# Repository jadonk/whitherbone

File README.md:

# whitherbone

Whithervanes: a neurotic, early worrying system are weathervanes controlled by the climate of fear on the Internet. They were first presented on five buildings in the seaside town of Folkestone, UK as part of the 2014 Folkestone Triennial. The Whithervanes parse newsfeeds looking for predetermined keywords related to fear (e.g. natural disaster, economic collapse, war, etc.) When fear is encountered the chickens respond by rotating away at increasing speeds from fear hot-spots and illuminating different colors triggered by specific levels of fear. Subsequently, 3 more full-size Whithervanes have been commissioned by Locust Projects in Miami for 2018.

We've been asked many times how people can have their own Whithervane. So, we are making the Whithervanes Open Hardware Kit. A prototype version was included in the “Are you talking to me?” exhibition currently in St. Etienne, France. We want to make the Whithervanes Open Hardware Kit a PocketBeagle derivative (Whitherbone), and need some help to do this.

http://www.whithervanes.com/

## Fan
| Pin | Signal |
| --- | ------ |
| 1   | GND    |
| 2   | +5V    |
| 3   | +5V    |
| 4   | GND    |

## Neopixel ring (LED)

| Pin | Signal | CPU ball | PRU  | SPI    | GPIO | 
| --- | ------ | -------- | ---- | ------ | ---- |
| 1   | GND    |          |      |        |      | 
| 2   | Data (DOUT)  | B2       | 0.2  | 1-MOSI | 112  | 
| 3   | +5V    |          |      |        |      | 
| 4   | GND    |          |      |        |      | 

## Motor

### Connector

| Pin | Signal       | Wires  |
| --- | ------------ | ------ |
| 1   | Coil 1+ (A+) | Red    |
| 2   | Coil 1- (A-) | Green  |
| 3   | Coil 2- (B-) | Blue   |
| 4   | Coil 2+ (B+) | Yellow | 

### Control signals

| Ball | GPIO | Signal |
| ---- | ---- | ------ |
| T4   | 22   | Step |
| P5   | 23   | Direction |
| R5   | 26   | Reset |
| T5   | 27   | uS1 |
| P6   | 44   | uS2 |
| R6   | 45   | uS3 |
| T6   | 46   | Enable |
| P7   | 47   | Sleep

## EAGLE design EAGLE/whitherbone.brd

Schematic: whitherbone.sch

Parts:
ANT1, ANT2: RECE.20279.001E.01; U-FL3P-SMD-2.6X2.6X1.0MM
C1: TLJB227M006R0500; AVX-B
C2, C8, C26, C38, C84: 1uF 10V; C0402
C3, C7: 47uF DNP; C1206
C4, C5, C18, C29, C30, C32, C33, C35, C36, C70, C74, C75, C79, C82, C83: 10uF 25V; C0805
C6, C20, C25, C27, C28, C31, C34, C44, C53, C61, C62, C63, C64, C65, C66, C69, C71, C72, C73, C76, C77, C78, C80, C81: 100nF 25V; C0402
C9, C10: 10pF; C0402
C11: 1nF 1000V; C1206
C12, C13, C14, C15: 18pF 50V; C0402
C16, C24: 100uF 16V; C1210
C17, C19, C56, C68: 100nF 50V; C0805
C21, C22: 22uF 16V; C1206
C23: 75pF 50V; C0402
C37, C40: DNI; C0402
C39, C41, C42, C43, C45, C46, C47, C49, C50, C52, C54, C55, C57, C58, C59, C60: 33pF 50V; C0402
C48, C51: 47uF 25V; ELECTRO-SMD-C-6MM
C67: 220nF; C0402
D1, D5, D6, D7, D8: Red; LED-0603
D2, D3, D4: Green; LED-0603
D9, D10, D11, D12, D13: DF2S6.8FS; SOD-923
F1: MF-FSMF010X; F0603
FUD1, FUD2, FUD3, FUD4, FUD5, FUD6: FIDUCIAL; FIDUCIAL_40MIL
IC1, IC2: TPD4S012DRYR; SON6-0.5-1.45X1X0.55MM
J1: ST-USB-01H2; MICRO-USB5+5P-SMD-0.65-7.2X5.06MM
J2: DC-044; DCJ3P-11.6X9.6X7.0MM
J3: ST-TF-003J; MICRO-SD9+4P-SMD-16.1X14.5X1.85MM
J4: 6p-2.54 DNP; H6-2.54
J5: WY-1223; H4-2.54-10.2X5.6MM
J6: ST-HD-010; HDMI19P-0.5-15X12.15X6.18MM
J7, J8: 2510S-4P(T); H4-2.54
JP2: ST-USB-003A; USB4+2-2.0-90D
L1, L2, L7, L8, L9: BLM15PD121SN1D; L0402
L3: IHLP3232DZER100M01; INT2-7.268-8.64X8.18X4MM
L4, L5: BLM21PG331SN1D; L0805
L6: LQH44PN1R0NP0L; L4.4X3.0MM
L10: WPN201610MR47MT; L201610
MGT1, MGT2, MGT3, MGT4: MOUNTING_HOLE
Q1, Q2, Q3: BSS138W-7-F; SOT-323
Q4: MMBT2907A; SOT-323
R1, R2, R18, R51, R52, R53, R54: 1.5k 1%; R0402
R3, R21, R62, R69, R70: 10k 1%; R0402
R4, R6, R7, R8, R9, R10, R63, R67, R68, R71, R72, R73, R74, R75, R81, R82, R83, R84, R87, R88, R89, R90, R91, R92, R93, R94, R98, R100, R106, R108, R109, R112, R119: 10k; R0402
R5, R11, R12, R31, R79, R96: 1k; R0402
R13, R14, R15, R16, R19, R22, R25, R26, R27, R28, R29: 33R; R0402
R17: 499R; R0402
R20: 40.2k 1%; R0402
R23, R24, R47, R64, R65, R66, R85, R116, R117, R118: 0R; R0402
R30: DNP 10k; R0402
R32: 100K, 1%, DNI; R0402
R33, R34, R35, R36, R37, R38, R39, R40, R41, R42, R43, R44, R45, R46, R49, R50, R58, R60, R80, R113, R114: 100k 1%; R0402
R48, R97: 0R; R1206
R55: 1M 1%; R0402
R56: 1M, 1%, DNI; R0402
R57: 560k 1%; R0402
R59: 49.9R 1%; R0402
R61: 13.3k 1%; R0402
R76: 51k 1%; R0402
R77: 1.3k 1%; R0402
R78: 240k 1%; R0402
R86, R101: DNP; R0402
R95, R102, R103, R115: 22R; R0402
R99: 5.6K 1%; R0402
R104, R105: 2k; R0402
R107: 33k; R0402
R110, R111: 0.1R; R1206
SW1, SW2: SKRPABE010; BUTTON4P-SMD-4.5X3.2X2.5MM
TP1: PAD-TEST-POINT'4545'; TP_4545
TP2, TP3, TP4, TP9, TP11, TP12, TP13, TP14, TP15, TP16, TP21, TP22, TP23, TP24: TPB0,65; TP_B0,65
TP5, TP6, TP7, TP8, TP26: TESTPAD/W_HOLE_1X1
TP10, TP34: TEST-POINT-D65/35; TP-D65/35MIL
TP17, TP18, TP19, TP20, TP25, TP27, TP28, TP29, TP30, TP31, TP32: TEST-POINT'4545'; TP-D45MIL
U1: OSD3358-512M-BSM; BGA256-1.27-21X21MM
U2: SN74LVC1G07DCKR; 5P-SMD-2X1.2X1MM
U3: ATL431AIDBZR; SOT-23
U4: WL1835MODGBMOCT; MODULE100P-0.7-13.5X13.2MM
U5: APX811-44UG-7; SOT143-R
U6: TPS54302; SOT-23-6
U7: TPS2051BDGNR; MSOP8-0.65-3X3MM
U8, U16: TLV62569DBVT; SOT-23-5
U9: SN74LVC1G125DCKR; SOT-353
U10: SN74LVC2G241DCUR; DCU8
U11: IT66121FN; QFN64-0.5-9X9MM
U12: A4988SETTR-T; QFN-28-5MM
U13, U14: ESD-RCLAMP0524P; ESD10P-0.5-2.5X1X0.58MM
VR1: EVM3GSX50B14; ADJR3-SMD-3.6X3.3MM
X1: ST3215SB32768H5HPWAA; X2-SMD-3.2X1.5X0.55MM
Y1: CX3225GB24000P0HPQCC; CRYSTAL-TXC-7A

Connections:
1.8V-WIFI: C2.1, C7.2, C8.1, L1.2, R4.1, R6.1, R7.1, R8.1, R9.1, R10.1, R30.1, U4.38 (VIO)
3.3V-WIFI: C3.2, C4.1, C5.1, C6.1, L2.2, R5.2, R11.2, R12.2, U4.46 (VBAT_IN1), U4.47 (VBAT_IN2)
12VDC: C48.+, C51.+, C68.2, R97.2, U12.22 (VBB1), U12.28 (VBB2)
AGND: C25.2, C27.2, C28.2, R66.2, U1.A9 (AGND_ADC)
AIN7: U1.D6 (PMIC_MUX_OUT), U1.D7 (AIN7)
BAT_SENSE: TP6.P$1, U1.N7 (PMIC_BAT_SENSE)
BT_EN: Q3.1 (G), U1.H15 (MII1_TXD0), U4.41 (BT_EN)
BT_HCI_CTS: R14.2, U1.D13 (MDC)
BT_HCI_RTS: R13.2, U1.E13 (MDIO)
BT_HCI_RX: R16.2, U1.D15 (MII1_RXD2)
BT_HCI_TX: R15.2, U1.D14 (MII1_RXD3)
B_UART0_RX: J4.4, R80.2, U10.2 (1A)
B_UART0_TX: J4.5, U10.3 (2Y)
CEC: D12.1 (2), J6.13 (CE_REMOTE), R106.2, U11.17 (CEC)
CGND: C11.2, J1.P1 (GND), J1.P3 (GND), J1.P4 (GND), J1.P5 (GND), J1.P6 (GND), J3.G2, J3.G3, J3.G4 (G3), J6.PAD (SHELL1), J6.PAD1 (SHELL2), J6.PAD2 (SHELL3), J6.PAD3 (SHELL4), JP2.SG1 (GND), JP2.SG2 (GND), MGT1.P$1, MGT2.P$1, MGT3.P$1, MGT4.P$1, R48.2
CK_N: J6.12 (CK-), U11.21 (TXCM), U14.5, U14.6
CK_P: J6.10 (CK+), U11.22 (TXCP), U14.4, U14.7
CLKOUT2: C37.2, R79.2, R96.2, U4.36 (EXT_32K)
COILA+: J5.1, U12.21 (OUT1B)
COILA-: J5.2, U12.24 (OUT1A)
COILB+: J5.4, U12.1 (OUT2B)
COILB-: J5.3, U12.26 (OUT2A)
CUR_REF: U12.17 (REF), VR1.2 (3)
D0_N: J6.9 (D0-), U11.24 (TX0M), U14.2, U14.9
D0_P: J6.7 (D0+), U11.25 (TX0P), U14.1, U14.10
D1_N: J6.6 (D1-), U11.26 (TX1M), U13.5, U13.6
D1_P: J6.4 (D1+), U11.27 (TX1P), U13.4, U13.7
D2_N: J6.3 (D2-), U11.29 (TX2M), U13.2, U13.9
D2_P: J6.1 (D2+), U11.30 (TX2P), U13.1, U13.10
DDC_SCL: D9.1 (2), J6.15 (DDC_CLK), R102.2, R104.2
DDC_SDA: D10.1 (2), J6.16 (DDC_DATA), R103.2, R105.2
DIR(GPIO23): R88.1, U1.P5 (GPMC_AD9), U12.19 (DIR)
EEPROM_WP: TP10.P1, U1.M2 (EEPROM_WP), U1.N3 (GPMC_BEN0_CLE)
ENABLE(GPIO46): R94.1, U1.T6 (GPMC_AD14), U12.2 (ENABLE)
GND: ANT1.GND1, ANT1.GND2, ANT2.GND1, ANT2.GND2, C1.-, C2.2, C3.1, C4.2, C5.2, C6.2, C7.1, C8.2, C11.1, C16.1, C17.1, C18.1, C20.2, C21.1, C22.1, C24.2, C26.1, C29.1, C30.1, C31.2, C32.2, C33.1, C34.2, C35.1, C36.1, C37.1, C38.1, C39.2, C40.1, C41.2, C42.2, C43.2, C44.1, C45.2, C46.2, C47.2, C48.-, C49.2, C50.2, C51.-, C52.2, C53.2, C54.2, C55.2, C57.2, C58.2, C59.2, C60.2, C61.1, C62.1, C63.1, C64.1, C65.1, C66.1, C67.2, C69.1, C70.1, C71.1, C72.1, C73.1, C74.1, C75.1, C76.1, C77.1, C78.1, C79.1, C80.1, C81.1, C82.1, C83.1, C84.1, D9.2 (1), D10.2 (1), D11.2 (1), D12.2 (1), D13.2 (1), IC1.4 (GND), IC2.4 (GND), J1.5 (GND), J2.-, J2.CDN, J3.6 (VSS), J4.1, J6.2 (D2_SHIELD), J6.5 (D1_SHIELD), J6.8 (D0_SHIELD), J6.11 (CK_SHIELD), J6.17 (GND), J7.1, J7.4, J8.1, J8.4, JP2.4 (GND), Q1.2 (S), Q2.2 (S), Q3.2 (S), R3.2, R18.2, R32.1, R33.1, R35.1, R36.1, R37.1, R38.1, R39.1, R40.1, R41.1, R42.1, R43.1, R46.1, R48.1, R49.1, R50.1, R51.2, R52.2, R53.2, R54.2, R58.1, R61.1, R62.2, R64.1, R70.1, R77.1, R79.1, R80.1, R94.2, R98.2, R99.1, R101.1, R107.1, R108.2, R109.1, R110.1, R111.1, R114.1, R119.2, SW1.1, SW1.2, SW2.1, SW2.2, TP8.P$1, U1.D8 (DGND), U1.D9 (DGND), U1.E5 (DGND), U1.E6 (DGND), U1.E7 (DGND), U1.E8 (DGND), U1.E9 (DGND), U1.E10 (DGND), U1.E11 (DGND), U1.E12 (DGND), U1.F5 (DGND), U1.F12 (DGND), U1.G5 (DGND), U1.G12 (DGND), U1.H4 (DGND), U1.H5 (DGND), U1.H12 (DGND), U1.H13 (DGND), U1.J4 (DGND), U1.J5 (DGND), U1.J12 (DGND), U1.J13 (DGND), U1.K5 (DGND), U1.K12 (DGND), U1.L5 (DGND), U1.L12 (DGND), U1.M5 (DGND), U1.M6 (DGND), U1.M7 (DGND), U1.M8 (DGND), U1.M9 (DGND), U1.M10 (DGND), U1.M11 (DGND), U1.M12 (DGND), U1.N8 (DGND), U1.N9 (DGND), U2.3 (GND), U4.1 (GND1), U4.7 (GND2), U4.9 (GND3), U4.15 (GND4), U4.16 (GND5), U4.17 (GND6), U4.19 (GND7), U4.20 (GND8), U4.23 (GND9), U4.24 (GND10), U4.28 (GND11), U4.29 (GND12), U4.30 (GND13), U4.31 (GND14), U4.33 (GND15), U4.34 (GND16), U4.35 (GND17), U4.37 (GND18), U4.39 (GND19), U4.44 (GND20), U4.45 (GND21), U4.48 (GND22), U4.49 (GND23), U4.54 (GND24), U4.55 (GND25), U4.59 (GND26), U4.61 (GND27), U4.63 (GND28), U4.64 (GND29), U4.G1, U4.G2, U4.G3, U4.G4, U4.G5, U4.G6, U4.G7, U4.G8, U4.G9, U4.G10, U4.G11, U4.G12, U4.G13, U4.G14, U4.G15, U4.G16, U4.G17, U4.G18, U4.G19, U4.G20, U4.G21, U4.G22, U4.G23, U4.G24, U4.G25, U4.G26, U4.G27, U4.G28, U4.G29, U4.G30, U4.G31, U4.G32, U4.G33, U4.G34, U4.G35, U4.G36, U5.1 (GND), U6.1 (GND), U7.1 (GND), U7.9 (THERMAL), U8.2 (GND), U9.1 (!OE), U9.3 (GND), U10.1 (*1OE), U10.4 (GND), U11.41 (D18), U11.42 (D17), U11.43 (D16), U11.50 (D9), U11.52 (D8), U11.59 (D2), U11.60 (D1), U11.61 (D0), U11.65 (GND), U12.3 (GND), U12.18 (GND), U12.PAD (GND_PAD), U13.3, U13.8, U14.3, U14.8, U16.2 (GND), VR1.1
HDMI_1V2: C61.2, C62.2, C63.2, C64.2, C65.2, C66.2, C82.2, C83.2, L10.2, R113.2, TP18.T, U11.8 (IVDD12), U11.18 (PVCC12), U11.23 (AVCC12), U11.28 (DVDD12), U11.35 (IVDD12), U11.56 (IVDD12)
HDMI_3V3: C69.2, C71.2, C73.2, C76.2, C77.2, C78.2, L8.2, R81.1, R82.1, R83.1, R84.1, R100.1, R106.1, R109.2, TP19.T, U11.1 (OVDD), U11.9 (VCC33), U11.13 (OVDD33), U11.19 (PVCC33), U11.34 (OVDD), U16.1 (EN)
HDMI_5V: C84.2, D11.1 (2), F1.2, J6.18 (+5V), R104.1, R105.1, TP20.T
HDMI_AUDBCLK: U1.A1 (MCASP0_ACLKX), U11.7 (SCK/MCLK)
HDMI_AUDDOUT: R85.1, R86.1, U1.B1 (MCASP0_AHCLKR)
HDMI_AUDWCLK: U1.A2 (MCASP0_FSX), U11.6 (WS)
HDMI_INT: R83.2, U1.T15 (GPMC_A9), U11.10 (INT)
HDMI_NRST: C38.2, R84.2, U11.33 (SYSRSTN)
HPD: D13.1 (2), J6.19 (HPD), R107.2, U11.14 (HPD)
I2C0_SCL: R1.1, U1.C10 (I2C0_SCL), U1.D10 (PMIC_SCL)
I2C0_SDA: R2.1, U1.C11 (I2C0_SDA), U1.D11 (PMIC_SDA)
I2C2_SCL: R82.2, U1.A10 (UART1_RTSN), U11.12 (PCSCL)
I2C2_SDA: R81.2, U1.B10 (UART1_CTSN), U11.11 (PCSDA)
LCD_DATA0: C60.1, R50.2, U1.G3 (LCD_DATA0), U11.58 (D3)
LCD_DATA1: C59.1, R49.2, U1.G2 (LCD_DATA1), U11.57 (D4)
LCD_DATA2: C58.1, R46.2, U1.G1 (LCD_DATA2), U11.55 (D5)
LCD_DATA3: C57.1, R45.1, U1.H3 (LCD_DATA3), U11.54 (D6)
LCD_DATA4: C55.1, R44.1, U1.H2 (LCD_DATA4), U11.53 (D7)
LCD_DATA5: C46.1, R43.2, U1.H1 (LCD_DATA5), U11.49 (D10)
LCD_DATA6: C45.1, R42.2, U1.J3 (LCD_DATA6), U11.48 (D11)
LCD_DATA7: C43.1, R41.2, U1.J2 (LCD_DATA7), U11.47 (D12)
LCD_DATA8: C42.1, R40.2, U1.J1 (LCD_DATA8), U11.46 (D13)
LCD_DATA9: C41.1, R39.2, U1.K3 (LCD_DATA9), U11.45 (D14)
LCD_DATA10: C39.1, R38.2, U1.K2 (LCD_DATA10), U11.44 (D15)
LCD_DATA11: C54.1, R37.2, U1.K1 (LCD_DATA11), U11.40 (D19)
LCD_DATA12: C52.1, R36.2, U1.L3 (LCD_DATA12), U11.39 (D20)
LCD_DATA13: C50.1, R35.2, U1.L2 (LCD_DATA13), U11.38 (D21)
LCD_DATA14: C49.1, R34.1, U1.L1 (LCD_DATA14), U11.37 (D22)
LCD_DATA15: C47.1, R33.2, U1.M3 (LCD_DATA15), U11.36 (D23)
LCD_DE: R118.2, U11.62 (DE)
LCD_HSYNC: R117.2, U11.63 (HSYNC)
LCD_PCLK: R115.2, U11.51 (PCLK)
LCD_VSYNC: R116.2, U11.64 (VSYNC)
LDO_PGOOD: TP22.TP, U1.N4 (PMIC_LDO_PGOOD), U1.N5 (RTC_PWRONRSTN)
MMC0_CD: J3.9 (CDN), R75.1, U1.C14 (SPI0_CS1)
MMC0_CLK: C40.2, J3.5 (SCLK), R71.1, R95.1
MMC0_CMD: J3.3 (DI), R68.1, U1.B16 (MMC0_CMD)
MMC0_DAT0: J3.7 (DO), R72.1, U1.A16 (MMC0_DAT0)
MMC0_DAT1: J3.8 (DATA1), R73.1, U1.A15 (MMC0_DAT1)
MMC0_DAT2: J3.1 (DATA2), R67.1, U1.C16 (MMC0_DAT2)
MMC0_DAT3: J3.2 (CS), R74.1, U1.C15 (MMC0_DAT3)
MS1(GPIO27): R89.1, U1.T5 (GPMC_AD11), U12.9 (MS1)
MS2(GPIO44): R90.1, U1.P6 (GPMC_AD12), U12.10 (MS2)
MS3(GPIO45): R91.1, U1.R6 (GPMC_AD13), U12.11 (MS3)
MVCC: C53.1, L7.2, R87.2, R88.2, R89.2, R90.2, R91.2, R92.2, R93.2, R112.1, U12.15 (VDD)
unnamed: J1.1 (VCC), R47.1
unnamed: D5.-, R51.1
unnamed: R31.2, U5.2 (RESET#)
unnamed: TP9.TP, U1.F4 (VDDS_DDR)
unnamed: C81.2, F1.1, L9.2
unnamed: D4.-, R18.1
unnamed: R20.2, R21.1, U3.1 (R)
unnamed: Q4.1 (B), R17.1, U3.2 (K)
unnamed: D6.-, R52.1
unnamed: D7.-, R53.1
unnamed: D8.-, R54.1
unnamed: ANT2.D, C10.1
unnamed: ANT1.D, C9.1
unnamed: TP2.TP, U1.G4 (VDD_CORE)
unnamed: TP3.TP, U1.F13 (VDD_MPU)
unnamed: R96.1, U1.B4 (XDMA_EVENT_INTR1)
unnamed: TP4.TP, U1.G13 (VDDS_PLL)
unnamed: R95.2, U1.B15 (MMC0_CLK)
unnamed: C9.2, U4.32 (RF_ANT1)
unnamed: C10.2, U4.18 (RF_ANT2)
unnamed: TP29.T, U4.26 (GPIO2)
unnamed: R23.1, SW2.3, SW2.4
unnamed: TP31.T, U4.42 (WL_UART_DBG)
unnamed: TP32.T, U4.43 (BT_UART_DBG)
unnamed: R24.1, U2.4 (Y)
unnamed: TP17.T, U4.56 (BT_AUD_IN)
unnamed: R119.1, TP25.T, U4.57 (BT_AUD_OUT)
unnamed: R3.1, U1.M16 (RTC_KALDO_ENN)
unnamed: TP28.T, U4.60 (BT_AUD_CLK)
unnamed: TP30.T, U4.27 (GPIO1)
unnamed: D2.-, Q2.3 (D)
unnamed: R100.2, R101.2, U11.32 (PCADR)
unnamed: R98.1, U11.31 (ENTEST)
unnamed: R102.1, U11.16 (DDCSCL)
unnamed: R103.1, U11.15 (DDCSDA)
unnamed: R86.2, U11.2 (I2S3/SPDIF)
unnamed: R85.2, U11.5 (I2S0)
unnamed: TP27.T, U4.58 (BT_AUD_FSYNC)
unnamed: R99.2, U11.20 (REXT)
unnamed: R19.1, U4.6 (WL_SDIO_CMD)
unnamed: D1.+, R5.1
unnamed: D1.-, Q1.3 (D)
unnamed: R111.2, U12.27 (SENSE2)
unnamed: R110.2, U12.23 (SENSE1)
unnamed: C56.1, U12.4 (CP1)
unnamed: C56.2, U12.5 (CP2)
unnamed: R108.1, U12.13 (ROSC)
unnamed: C67.1, U12.8 (VREG)
unnamed: C68.1, U12.6 (VCP)
unnamed: D3.-, Q3.3 (D)
unnamed: D2.+, R11.1
unnamed: D3.+, R12.1
unnamed: R112.2, VR1.3 (2)
unnamed: J7.2, U9.4 (Y)
unnamed: R29.1, R30.2, U4.14 (WLAN_IRQ)
unnamed: R28.1, U4.13 (WL_SDIO_D3)
unnamed: R27.1, U4.12 (WL_SDIO_D2)
unnamed: R26.1, U4.11 (WL_SDIO_D1)
unnamed: R25.1, U4.10 (WL_SDIO_D0)
unnamed: R22.1, U4.8 (WL_SDIO_CLK)
unnamed: R115.1, U1.F1 (LCD_PCLK)
unnamed: R116.1, U1.F3 (LCD_VSYNC)
unnamed: L10.1, U16.3 (SW)
unnamed: R113.1, R114.2, U16.5 (FB)
unnamed: R76.2, R78.2, U8.5 (FB)
unnamed: L6.1, U8.3 (SW)
unnamed: R76.1, R77.2
unnamed: R117.1, U1.F2 (LCD_HSYNC)
unnamed: R57.1, R58.2, U6.5 (EN)
unnamed: R118.1, U1.E1 (LCD_AC_BIAS_EN)
unnamed: C19.2, U6.6 (BOOT)
unnamed: C19.1, L3.1, U6.2 (SW)
unnamed: C23.1, R59.1, R60.2
unnamed: C23.2, R60.1, R61.2, U6.4 (FB)
unnamed: R13.1, U4.50 (BT_HCI_RTS)
unnamed: R14.1, U4.51 (BT_HCI_CTS)
unnamed: R15.1, U4.52 (BT_HCI_TX)
unnamed: R16.1, U4.53 (BT_HCI_RX)
OSC0_GND: C12.2, C13.2, U1.N15 (OSC0_GND)
OSC0_IN: C12.1, R55.2, U1.P16 (OSC0_IN), Y1.P$2 (2)
OSC0_OUT: C13.1, R55.1, U1.N16 (OSC0_OUT), Y1.P$1 (1)
OSC1_GND: C14.2, C15.2, U1.B5 (OSC1_GND)
OSC1_IN: C14.1, R56.2, U1.A6 (OSC1_IN), X1.2
OSC1_OUT: C15.1, R56.1, U1.A5 (OSC1_OUT), X1.1
PMIC_INT: TP24.TP, U1.D4 (EXTINTN), U1.E4 (PMIC_NINT)
PMIC_MUX_IN: R69.1, R70.2, U1.N13 (PMIC_MUX_IN)
PMIC_NRESET: TP34.P1, U1.M13 (PMIC_NRESET)
PMIC_NWAKEUP: TP23.TP, U1.L4 (PMIC_NWAKEUP), U1.M4 (EXT_WAKEUP)
PMIC_PGOOD: U1.N12 (PMIC_PGOOD), U1.P11 (PWRONRSTN), U2.2 (A)
PWR_BUT: SW1.3, SW1.4, U1.T11 (PMIC_PB_IN)
PWR_EN: TP21.TP, U1.N10 (PMIC_POWER_EN), U1.N11 (PMIC_PWR_EN)
PWR_IN_12V: C16.2, C17.2, C18.2, J2.+, R57.2, R97.1, TP1.T, U6.3 (VIN)
RESET: R23.2, R24.2, U5.3 (MR#)
RESET(GPIO26): R93.1, U1.R5 (GPMC_AD10), U12.12 (RESET)
SLEEP(GPIO47): R92.1, U1.P7 (GPMC_AD15), U12.14 (SLEEP)
STEP(GPIO22): R87.1, U1.T4 (GPMC_AD8), U12.16 (STEP)
SYS_5V: C24.1, U7.2 (IN1), U7.3 (IN2)
SYS_ADC_1P8V: C28.1, R65.2, U1.A7 (SYS_ADC_1P8V)
SYS_RESETN: R31.1, R32.2, TP26.P$1, U1.R11 (WARMRSTN)
SYS_RTC_1P8V: Q4.3 (C), R20.1, TP14.TP, U1.K11 (SYS_RTC_1P8V), U1.L11 (SYS_RTC_1P8V), U2.5 (VCC), U3.3 (A)
SYS_VDD1_3P3V: C32.1, C34.1, C44.2, C70.2, C72.2, J3.4 (VDD), L8.1, R1.2, R2.2, R34.2, R44.2, R45.2, R63.1, R67.2, R68.2, R69.2, R71.2, R72.2, R73.2, R74.2, R75.2, TP12.TP, U1.F6 (SYS_VDD1_3P3V), U1.F7 (SYS_VDD1_3P3V), U1.G6 (SYS_VDD1_3P3V), U1.G7 (SYS_VDD1_3P3V), U5.4 (VCC), U8.1 (EN), U10.7 (2OE), U10.8 (VCC)
SYS_VDD2_3P3V: D4.+, TP13.TP, U1.F11 (SYS_VDD2_3P3V), U1.G11 (SYS_VDD2_3P3V)
SYS_VDD3_3P3V: Q4.2 (E), R17.2, R21.2, TP16.TP, U1.F8 (SYS_VDD3_3P3V), U1.F9 (VDDSHV4), U1.G8 (SYS_VDD3_3P3V), U1.H7 (SYS_VDD3_3P3V), U1.H8 (SYS_VDD3_3P3V), U1.H9 (VDDSHV6), U1.J7 (SYS_VDD3_3P3V), U1.J8 (SYS_VDD3_3P3V), U1.J9 (VDDSHV1), U1.K8 (SYS_VDD3_3P3V), U1.K9 (VDDSHV2), U1.L8 (SYS_VDD3_3P3V), U1.L9 (VDDSHV3)
SYS_VDD_1P8V: L1.1, TP15.TP, U1.F10 (SYS_VDD_1P8V), U1.G9 (VDDSHV5), U1.G10 (SYS_VDD_1P8V), U1.H10 (SYS_VDD_1P8V), U1.H11 (SYS_VDD_1P8V), U1.J10 (SYS_VDD_1P8V), U1.J11 (SYS_VDD_1P8V), U1.K10 (SYS_VDD_1P8V), U1.L10 (SYS_VDD_1P8V)
SYS_VOUT: C74.2, C75.2, C79.2, C80.2, L9.1, TP11.TP, U1.K6 (SYS_VOUT), U1.K7 (SYS_VOUT), U1.L6 (SYS_VOUT), U1.L7 (SYS_VOUT), U16.4 (VIN)
TEMP_SENSE: TP7.P$1, U1.N6 (PMIC_TS)
TO_NEOPIXEL: U1.B2 (MCASP0_AXR0), U9.2 (A)
UART0_RX: U1.A12 (UART0_RXD), U10.6 (1Y)
UART0_TX: U1.B12 (UART0_TXD), U10.5 (2A)
USB0_DM: IC1.1 (D+), J1.2 (DM), U1.K16 (USB0_DM)
USB0_DP: IC1.2 (D-), J1.3 (DP), U1.K15 (USB0_DP)
USB0_ID: IC1.3 (ID), J1.4 (ID), U1.K14 (USB0_ID)
USB1_DM: IC2.1 (D+), JP2.2 (D-), U1.L16 (USB1_DM)
USB1_DP: IC2.2 (D-), JP2.3 (D+), U1.L15 (USB1_DP)
USB1_DRVVBUS: R62.1, U1.M14 (USB1_DRVVBUS), U7.4 (EN#)
USB1_ID: R64.2, U1.L14 (USB1_ID)
USB1_OC#: R63.2, U7.5 (OC#)
USB1_VBUS: L4.2, U1.M15 (USB1_VBUS)
USR0: D5.+, U1.P13 (GPMC_A5)
USR1: D6.+, U1.T14 (GPMC_A6)
USR2: D7.+, U1.R14 (GPMC_A7)
USR3: D8.+, U1.P14 (GPMC_A8)
VBUS.HOST: JP2.1 (VBUS), L5.2
VBUS.OUT: C31.1, IC2.6 (VBUS), L4.1, L5.1, U7.6 (OUT1), U7.7 (OUT2), U7.8 (OUT3)
VDD_3V3B: C35.2, C36.2, L2.1, L6.2, L7.1, R78.1
VDD_5V: C1.+, C21.2, C22.2, C26.2, C29.2, C30.2, C33.2, J7.3, J8.2, J8.3, L3.2, R59.2, U1.P10 (VIN_AC), U1.R10 (VIN_AC), U1.T10 (VIN_AC), U8.4 (VIN), U9.5 (VCC)
VDD_BAT: TP5.P$1, U1.P8 (VIN_BAT), U1.R8 (VIN_BAT), U1.T8 (VIN_BAT)
VDD_USB_5V: C20.1, IC1.6 (VBUS), R47.2, U1.J16 (USB0_VBUS), U1.P9 (VIN_USB), U1.R9 (VIN_USB), U1.T9 (VIN_USB)
VREFN: R66.1, U1.B9 (VREFN)
VREFP: C25.1, C27.1, R65.1, U1.B7 (VREFP)
WIFI_LED(GPIO3_01): Q1.1 (G), U1.F14 (MII1_CRS)
WL_EN: Q2.1 (G), U1.H16 (MII1_TX_CLK), U4.40 (WLAN_EN)
WL_IRQ: R29.2, U1.H14 (MII1_TXD1)
WL_SDIO_CLK: R9.2, R22.2, U1.D16 (MII1_RXD1)
WL_SDIO_CMD: R10.2, R19.2, U1.G14 (MII1_TX_EN)
WL_SDIO_D0: R4.2, R25.2, U1.F16 (MII1_RX_DV)
WL_SDIO_D1: R6.2, R26.2, U1.G15 (MII1_TXD3)
WL_SDIO_D2: R7.2, R27.2, U1.G16 (MII1_TXD2)
WL_SDIO_D3: R8.2, R28.2, U1.F15 (MII1_COL)

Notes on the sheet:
Power & Reset
Clocks, Analog & USB
SiP Interfaces
Boot configuration
HDMI
Micro SD card slot
User LEDs
USB Client
SiP GND & Misc
1/12
3/12
2/12
4/12
5/12
9/12
Mounting Holes
Fiducials
12/12
PCADR pull high: 0x9A PCADR pull low : 0x98
Differential impedance: 100 Ohm
Red
Green
Blue
ESD Protection Diodes close to HDMI Connector.
WiFi Module
USB Host
Neopixel Connector
FAN Connector
These signals are all 1.8V
Vout=0.6Vx(1+R1/R2)
I = 3A
I = 2A
I = 1A
I = 200mA
I = 100mA
I = 500mA

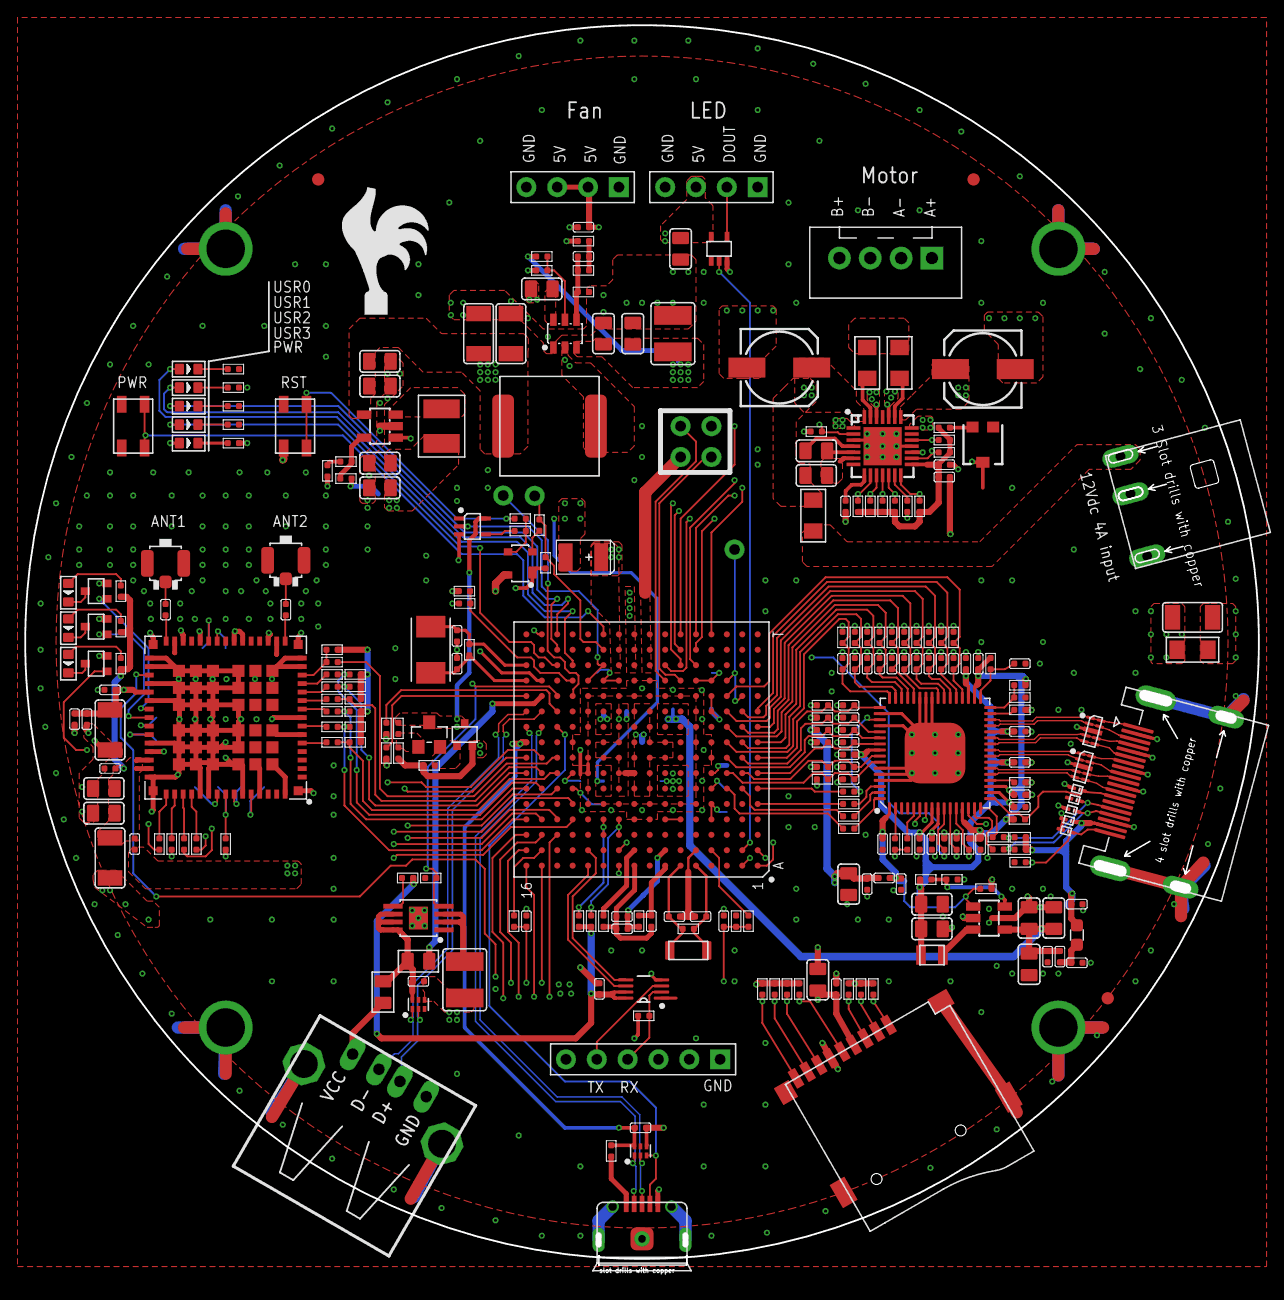
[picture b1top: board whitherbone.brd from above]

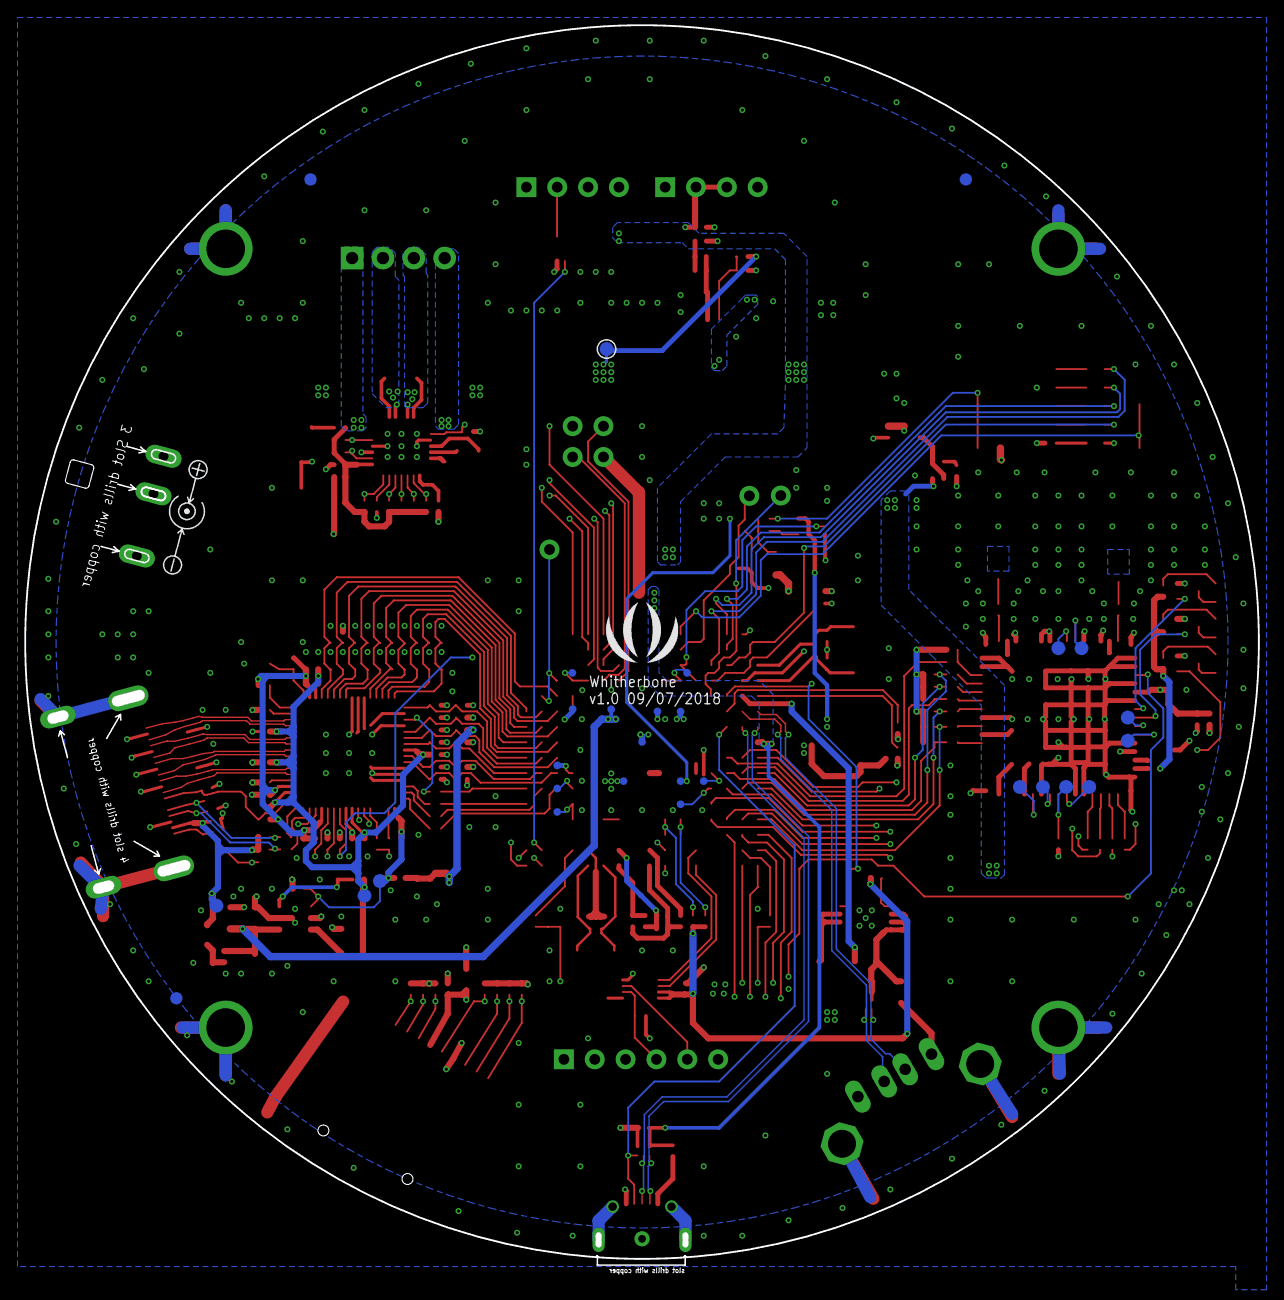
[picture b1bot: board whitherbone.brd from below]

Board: 4 copper layers, 101.6 x 102.1 mm, 308 parts (30 on the bottom side), 219 nets.

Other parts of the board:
U$1: SEEED-SILK-TNAME-280*268MIL

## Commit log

2017-12-11 Clone PocketBeagle A2a design
2017-12-11 Rename PocketBeagle to witherbone
2017-12-11 Hack in TFP410
2017-12-11 Download WL1835MOD from SnapEDA
2017-12-11 Add missed files
2017-12-11 Make sure name is whitherbone everywhere
2017-12-12 Add LICENSE
2018-01-04 SCH: label boot configuration
2018-07-13 Start EAGLE version based on BeagleBone Black Wireless
2018-07-14 Hooked up some stuff
2018-07-14 Connected WiFi/BT
2018-07-15 Add HDMI
2018-07-16 USR LED connections
2018-07-17 Power and other clean-up
2018-07-17 Stopping for the night
2018-07-17 Started motor driver
2018-07-17 Some minor power fixups
2018-07-17 Move WiFi signals to 1.8V and remove level shifters
2018-07-17 Copied BigEasyDriver
2018-07-17 Wired up BigEasyDriver
2018-07-17 Add connector for Neopixels (not yet connected)
2018-07-18 Connected NEOPIXEL connector
2018-07-18 Add quick decoupling cap for neopixel output
2018-07-18 Add quick fan connector
2018-07-18 Add a quick schematic PDF
2018-08-23 Use version from Seeed
2018-08-23 Add early placement
2018-09-12 Remove KiCAD version
2018-09-12 Update to latest from Seeed
    * Layout complete
    * Added mechanical drawing (DXF) for board
2018-09-12 Update LICENSE
    Removed any utilization of Michael Welling's work. No reason, it just wasn't used in this EAGLE version from Seeed and we dropped the KiCAD version for now. I left in Aron, because we might have some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
2018-11-13 Latest from Seeed
2018-11-13 Update latest from Seeed

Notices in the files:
EAGLE/whitherbone.sch:
licensed under a Creative Commons
parts and their libraries:
moudle-new: CC-BY-SA
